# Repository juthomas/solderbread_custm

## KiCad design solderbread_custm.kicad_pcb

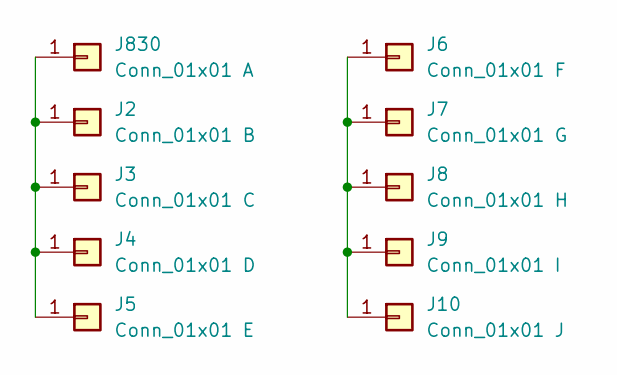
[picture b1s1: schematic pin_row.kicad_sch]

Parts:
J2: Conn_01x01 B; single_pin
J3: Conn_01x01 C; single_pin
J4: Conn_01x01 D; single_pin
J5: Conn_01x01 E; single_pin
J6: Conn_01x01 F; single_pin
J7: Conn_01x01 G; single_pin
J8: Conn_01x01 H; single_pin
J9: Conn_01x01 I; single_pin
J10: Conn_01x01 J; single_pin
J830: Conn_01x01 A; single_pin

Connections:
unnamed: J2.1, J3.1, J4.1, J5.1, J830.1
unnamed: J6.1, J7.1, J8.1, J9.1, J10.1

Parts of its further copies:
J11, J21, J31, J41, J51, J61, J71, J81, J91, J101, J111, J121, J131, J141, J151, J161, J171, J181, J191, J201, J211, J221, J231, J241, J251, J261, J271, J281, J291, J301, J311, J321, J331, J341, J351, J361, J371, J381, J391, J401, J411, J421, J431, J441, J451, J461, J471, J481, J491, J501, J511, J521, J531, J541, J551, J561, J571, J581, J591, J601, J611, J621: Conn_01x01 A; single_pin
J12, J22, J32, J42, J52, J62, J72, J82, J92, J102, J112, J122, J132, J142, J152, J162, J172, J182, J192, J202, J212, J222, J232, J242, J252, J262, J272, J282, J292, J302, J312, J322, J332, J342, J352, J362, J372, J382, J392, J402, J412, J422, J432, J442, J452, J462, J472, J482, J492, J502, J512, J522, J532, J542, J552, J562, J572, J582, J592, J602, J612, J622: Conn_01x01 B; single_pin
J13, J23, J33, J43, J53, J63, J73, J83, J93, J103, J113, J123, J133, J143, J153, J163, J173, J183, J193, J203, J213, J223, J233, J243, J253, J263, J273, J283, J293, J303, J313, J323, J333, J343, J353, J363, J373, J383, J393, J403, J413, J423, J433, J443, J453, J463, J473, J483, J493, J503, J513, J523, J533, J543, J553, J563, J573, J583, J593, J603, J613, J623: Conn_01x01 C; single_pin
J14, J24, J34, J44, J54, J64, J74, J84, J94, J104, J114, J124, J134, J144, J154, J164, J174, J184, J194, J204, J214, J224, J234, J244, J254, J264, J274, J284, J294, J304, J314, J324, J334, J344, J354, J364, J374, J384, J394, J404, J414, J424, J434, J444, J454, J464, J474, J484, J494, J504, J514, J524, J534, J544, J554, J564, J574, J584, J594, J604, J614, J624: Conn_01x01 D; single_pin
J15, J25, J35, J45, J55, J65, J75, J85, J95, J105, J115, J125, J135, J145, J155, J165, J175, J185, J195, J205, J215, J225, J235, J245, J255, J265, J275, J285, J295, J305, J315, J325, J335, J345, J355, J365, J375, J385, J395, J405, J415, J425, J435, J445, J455, J465, J475, J485, J495, J505, J515, J525, J535, J545, J555, J565, J575, J585, J595, J605, J615, J625: Conn_01x01 E; single_pin
J16, J26, J36, J46, J56, J66, J76, J86, J96, J106, J116, J126, J136, J146, J156, J166, J176, J186, J196, J206, J216, J226, J236, J246, J256, J266, J276, J286, J296, J306, J316, J326, J336, J346, J356, J366, J376, J386, J396, J406, J416, J426, J436, J446, J456, J466, J476, J486, J496, J506, J516, J526, J536, J546, J556, J566, J576, J586, J596, J606, J616, J626: Conn_01x01 F; single_pin
J17, J27, J37, J47, J57, J67, J77, J87, J97, J107, J117, J127, J137, J147, J157, J167, J177, J187, J197, J207, J217, J227, J237, J247, J257, J267, J277, J287, J297, J307, J317, J327, J337, J347, J357, J367, J377, J387, J397, J407, J417, J427, J437, J447, J457, J467, J477, J487, J497, J507, J517, J527, J537, J547, J557, J567, J577, J587, J597, J607, J617, J627: Conn_01x01 G; single_pin
J18, J28, J38, J48, J58, J68, J78, J88, J98, J108, J118, J128, J138, J148, J158, J168, J178, J188, J198, J208, J218, J228, J238, J248, J258, J268, J278, J288, J298, J308, J318, J328, J338, J348, J358, J368, J378, J388, J398, J408, J418, J428, J438, J448, J458, J468, J478, J488, J498, J508, J518, J528, J538, J548, J558, J568, J578, J588, J598, J608, J618, J628: Conn_01x01 H; single_pin
J19, J29, J39, J49, J59, J69, J79, J89, J99, J109, J119, J129, J139, J149, J159, J169, J179, J189, J199, J209, J219, J229, J239, J249, J259, J269, J279, J289, J299, J309, J319, J329, J339, J349, J359, J369, J379, J389, J399, J409, J419, J429, J439, J449, J459, J469, J479, J489, J499, J509, J519, J529, J539, J549, J559, J569, J579, J589, J599, J609, J619, J629: Conn_01x01 I; single_pin
J20, J30, J40, J50, J60, J70, J80, J90, J100, J110, J120, J130, J140, J150, J160, J170, J180, J190, J200, J210, J220, J230, J240, J250, J260, J270, J280, J290, J300, J310, J320, J330, J340, J350, J360, J370, J380, J390, J400, J410, J420, J430, J440, J450, J460, J470, J480, J490, J500, J510, J520, J530, J540, J550, J560, J570, J580, J590, J600, J610, J620, J630: Conn_01x01 J; single_pin

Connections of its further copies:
unnamed: J11.1, J12.1, J13.1, J14.1, J15.1
unnamed: J16.1, J17.1, J18.1, J19.1, J20.1
unnamed: J21.1, J22.1, J23.1, J24.1, J25.1
unnamed: J26.1, J27.1, J28.1, J29.1, J30.1
unnamed: J31.1, J32.1, J33.1, J34.1, J35.1
unnamed: J36.1, J37.1, J38.1, J39.1, J40.1
unnamed: J41.1, J42.1, J43.1, J44.1, J45.1
unnamed: J46.1, J47.1, J48.1, J49.1, J50.1
unnamed: J51.1, J52.1, J53.1, J54.1, J55.1
unnamed: J56.1, J57.1, J58.1, J59.1, J60.1
unnamed: J61.1, J62.1, J63.1, J64.1, J65.1
unnamed: J66.1, J67.1, J68.1, J69.1, J70.1
unnamed: J71.1, J72.1, J73.1, J74.1, J75.1
unnamed: J76.1, J77.1, J78.1, J79.1, J80.1
unnamed: J81.1, J82.1, J83.1, J84.1, J85.1
unnamed: J86.1, J87.1, J88.1, J89.1, J90.1
unnamed: J91.1, J92.1, J93.1, J94.1, J95.1
unnamed: J96.1, J97.1, J98.1, J99.1, J100.1
unnamed: J101.1, J102.1, J103.1, J104.1, J105.1
unnamed: J106.1, J107.1, J108.1, J109.1, J110.1
unnamed: J111.1, J112.1, J113.1, J114.1, J115.1
unnamed: J116.1, J117.1, J118.1, J119.1, J120.1
unnamed: J121.1, J122.1, J123.1, J124.1, J125.1
unnamed: J126.1, J127.1, J128.1, J129.1, J130.1
unnamed: J131.1, J132.1, J133.1, J134.1, J135.1
unnamed: J136.1, J137.1, J138.1, J139.1, J140.1
unnamed: J141.1, J142.1, J143.1, J144.1, J145.1
unnamed: J146.1, J147.1, J148.1, J149.1, J150.1
unnamed: J151.1, J152.1, J153.1, J154.1, J155.1
unnamed: J156.1, J157.1, J158.1, J159.1, J160.1
unnamed: J161.1, J162.1, J163.1, J164.1, J165.1
unnamed: J166.1, J167.1, J168.1, J169.1, J170.1
unnamed: J171.1, J172.1, J173.1, J174.1, J175.1
unnamed: J176.1, J177.1, J178.1, J179.1, J180.1
unnamed: J181.1, J182.1, J183.1, J184.1, J185.1
unnamed: J186.1, J187.1, J188.1, J189.1, J190.1
unnamed: J191.1, J192.1, J193.1, J194.1, J195.1
unnamed: J196.1, J197.1, J198.1, J199.1, J200.1
unnamed: J201.1, J202.1, J203.1, J204.1, J205.1
unnamed: J206.1, J207.1, J208.1, J209.1, J210.1
unnamed: J211.1, J212.1, J213.1, J214.1, J215.1
unnamed: J216.1, J217.1, J218.1, J219.1, J220.1
unnamed: J221.1, J222.1, J223.1, J224.1, J225.1
unnamed: J226.1, J227.1, J228.1, J229.1, J230.1
unnamed: J231.1, J232.1, J233.1, J234.1, J235.1
unnamed: J236.1, J237.1, J238.1, J239.1, J240.1
unnamed: J241.1, J242.1, J243.1, J244.1, J245.1
unnamed: J246.1, J247.1, J248.1, J249.1, J250.1
unnamed: J251.1, J252.1, J253.1, J254.1, J255.1
unnamed: J256.1, J257.1, J258.1, J259.1, J260.1
unnamed: J261.1, J262.1, J263.1, J264.1, J265.1
unnamed: J266.1, J267.1, J268.1, J269.1, J270.1
unnamed: J271.1, J272.1, J273.1, J274.1, J275.1
unnamed: J276.1, J277.1, J278.1, J279.1, J280.1
unnamed: J281.1, J282.1, J283.1, J284.1, J285.1
unnamed: J286.1, J287.1, J288.1, J289.1, J290.1
unnamed: J291.1, J292.1, J293.1, J294.1, J295.1
unnamed: J296.1, J297.1, J298.1, J299.1, J300.1
unnamed: J301.1, J302.1, J303.1, J304.1, J305.1
unnamed: J306.1, J307.1, J308.1, J309.1, J310.1
unnamed: J311.1, J312.1, J313.1, J314.1, J315.1
unnamed: J316.1, J317.1, J318.1, J319.1, J320.1
unnamed: J321.1, J322.1, J323.1, J324.1, J325.1
unnamed: J326.1, J327.1, J328.1, J329.1, J330.1
unnamed: J331.1, J332.1, J333.1, J334.1, J335.1
unnamed: J336.1, J337.1, J338.1, J339.1, J340.1
unnamed: J341.1, J342.1, J343.1, J344.1, J345.1
unnamed: J346.1, J347.1, J348.1, J349.1, J350.1
unnamed: J351.1, J352.1, J353.1, J354.1, J355.1
unnamed: J356.1, J357.1, J358.1, J359.1, J360.1
unnamed: J361.1, J362.1, J363.1, J364.1, J365.1
unnamed: J366.1, J367.1, J368.1, J369.1, J370.1
unnamed: J371.1, J372.1, J373.1, J374.1, J375.1
unnamed: J376.1, J377.1, J378.1, J379.1, J380.1
unnamed: J381.1, J382.1, J383.1, J384.1, J385.1
unnamed: J386.1, J387.1, J388.1, J389.1, J390.1
unnamed: J391.1, J392.1, J393.1, J394.1, J395.1
unnamed: J396.1, J397.1, J398.1, J399.1, J400.1
unnamed: J401.1, J402.1, J403.1, J404.1, J405.1
unnamed: J406.1, J407.1, J408.1, J409.1, J410.1
unnamed: J411.1, J412.1, J413.1, J414.1, J415.1
unnamed: J416.1, J417.1, J418.1, J419.1, J420.1
unnamed: J421.1, J422.1, J423.1, J424.1, J425.1
unnamed: J426.1, J427.1, J428.1, J429.1, J430.1
unnamed: J431.1, J432.1, J433.1, J434.1, J435.1
unnamed: J436.1, J437.1, J438.1, J439.1, J440.1
unnamed: J441.1, J442.1, J443.1, J444.1, J445.1
unnamed: J446.1, J447.1, J448.1, J449.1, J450.1
unnamed: J451.1, J452.1, J453.1, J454.1, J455.1
unnamed: J456.1, J457.1, J458.1, J459.1, J460.1
unnamed: J461.1, J462.1, J463.1, J464.1, J465.1
unnamed: J466.1, J467.1, J468.1, J469.1, J470.1
unnamed: J471.1, J472.1, J473.1, J474.1, J475.1
unnamed: J476.1, J477.1, J478.1, J479.1, J480.1
unnamed: J481.1, J482.1, J483.1, J484.1, J485.1
unnamed: J486.1, J487.1, J488.1, J489.1, J490.1
unnamed: J491.1, J492.1, J493.1, J494.1, J495.1
unnamed: J496.1, J497.1, J498.1, J499.1, J500.1
unnamed: J501.1, J502.1, J503.1, J504.1, J505.1
unnamed: J506.1, J507.1, J508.1, J509.1, J510.1
unnamed: J511.1, J512.1, J513.1, J514.1, J515.1
unnamed: J516.1, J517.1, J518.1, J519.1, J520.1
unnamed: J521.1, J522.1, J523.1, J524.1, J525.1
unnamed: J526.1, J527.1, J528.1, J529.1, J530.1
unnamed: J531.1, J532.1, J533.1, J534.1, J535.1
unnamed: J536.1, J537.1, J538.1, J539.1, J540.1
unnamed: J541.1, J542.1, J543.1, J544.1, J545.1
unnamed: J546.1, J547.1, J548.1, J549.1, J550.1
unnamed: J551.1, J552.1, J553.1, J554.1, J555.1
unnamed: J556.1, J557.1, J558.1, J559.1, J560.1
unnamed: J561.1, J562.1, J563.1, J564.1, J565.1
unnamed: J566.1, J567.1, J568.1, J569.1, J570.1
unnamed: J571.1, J572.1, J573.1, J574.1, J575.1
unnamed: J576.1, J577.1, J578.1, J579.1, J580.1
unnamed: J581.1, J582.1, J583.1, J584.1, J585.1
unnamed: J586.1, J587.1, J588.1, J589.1, J590.1
unnamed: J591.1, J592.1, J593.1, J594.1, J595.1
unnamed: J596.1, J597.1, J598.1, J599.1, J600.1
unnamed: J601.1, J602.1, J603.1, J604.1, J605.1
unnamed: J606.1, J607.1, J608.1, J609.1, J610.1
unnamed: J611.1, J612.1, J613.1, J614.1, J615.1
unnamed: J616.1, J617.1, J618.1, J619.1, J620.1
unnamed: J621.1, J622.1, J623.1, J624.1, J625.1
unnamed: J626.1, J627.1, J628.1, J629.1, J630.1

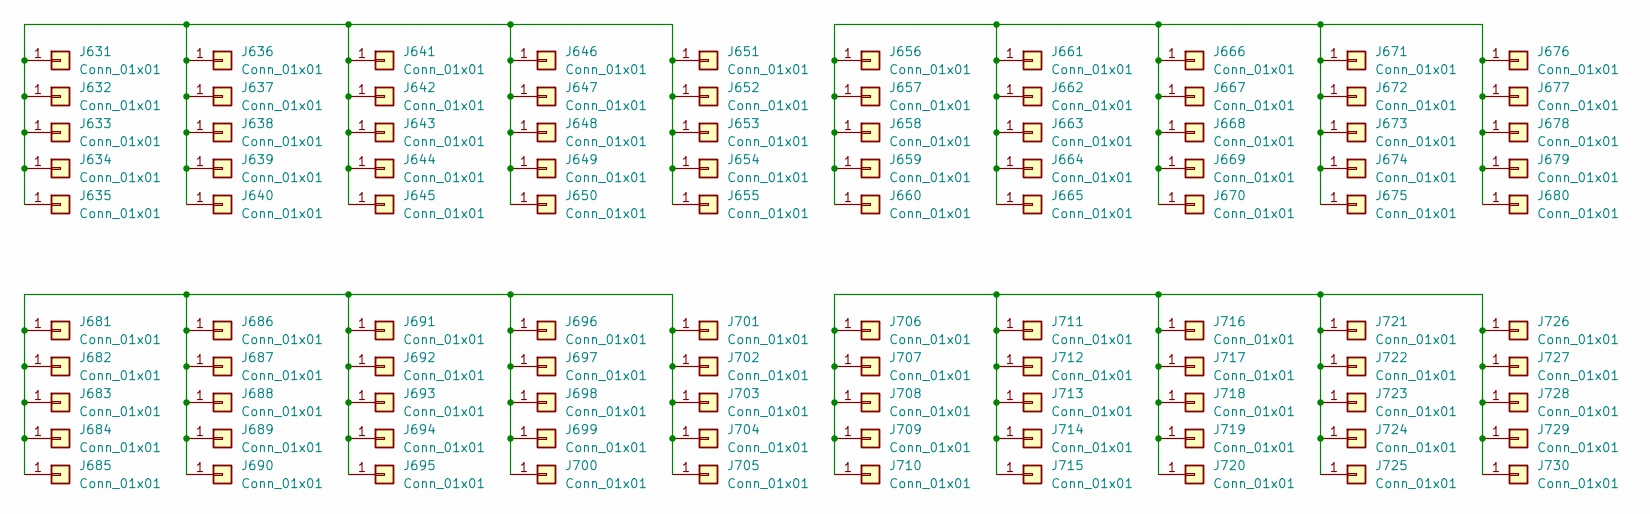
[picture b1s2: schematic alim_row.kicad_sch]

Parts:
J631, J632, J633, J634, J635, J636, J637, J638, J639, J640, J641, J642, J643, J644, J645, J646, J647, J648, J649, J650, J651, J652, J653, J654, J655, J656, J657, J658, J659, J660, J661, J662, J663, J664, J665, J666, J667, J668, J669, J670, J671, J672, J673, J674, J675, J676, J677, J678, J679, J680, J681, J682, J683, J684, J685, J686, J687, J688, J689, J690, J691, J692, J693, J694, J695, J696, J697, J698, J699, J700, J701, J702, J703, J704, J705, J706, J707, J708, J709, J710, J711, J712, J713, J714, J715, J716, J717, J718, J719, J720, J721, J722, J723, J724, J725, J726, J727, J728, J729, J730: Conn_01x01; single_pin

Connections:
unnamed: J631.1, J632.1, J633.1, J634.1, J635.1, J636.1, J637.1, J638.1, J639.1, J640.1, J641.1, J642.1, J643.1, J644.1, J645.1, J646.1, J647.1, J648.1, J649.1, J650.1, J651.1, J652.1, J653.1, J654.1, J655.1
unnamed: J656.1, J657.1, J658.1, J659.1, J660.1, J661.1, J662.1, J663.1, J664.1, J665.1, J666.1, J667.1, J668.1, J669.1, J670.1, J671.1, J672.1, J673.1, J674.1, J675.1, J676.1, J677.1, J678.1, J679.1, J680.1
unnamed: J681.1, J682.1, J683.1, J684.1, J685.1, J686.1, J687.1, J688.1, J689.1, J690.1, J691.1, J692.1, J693.1, J694.1, J695.1, J696.1, J697.1, J698.1, J699.1, J700.1, J701.1, J702.1, J703.1, J704.1, J705.1
unnamed: J706.1, J707.1, J708.1, J709.1, J710.1, J711.1, J712.1, J713.1, J714.1, J715.1, J716.1, J717.1, J718.1, J719.1, J720.1, J721.1, J722.1, J723.1, J724.1, J725.1, J726.1, J727.1, J728.1, J729.1, J730.1

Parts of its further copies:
J1, J731, J732, J733, J734, J735, J736, J737, J738, J739, J740, J741, J742, J743, J744, J745, J746, J747, J748, J749, J750, J751, J752, J753, J754, J755, J756, J757, J758, J759, J760, J761, J762, J763, J764, J765, J766, J767, J768, J769, J770, J771, J772, J773, J774, J775, J776, J777, J778, J779, J780, J781, J782, J783, J784, J785, J786, J787, J788, J789, J790, J791, J792, J793, J794, J795, J796, J797, J798, J799, J800, J801, J802, J803, J804, J805, J806, J807, J808, J809, J810, J811, J812, J813, J814, J815, J816, J817, J818, J819, J820, J821, J822, J823, J824, J825, J826, J827, J828, J829: Conn_01x01; single_pin

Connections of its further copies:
unnamed: J1.1, J731.1, J732.1, J733.1, J734.1, J740.1, J741.1, J742.1, J743.1, J744.1, J750.1, J751.1, J752.1, J753.1, J754.1, J760.1, J761.1, J762.1, J763.1, J764.1, J770.1, J771.1, J772.1, J773.1, J774.1
unnamed: J735.1, J736.1, J737.1, J738.1, J739.1, J745.1, J746.1, J747.1, J748.1, J749.1, J755.1, J756.1, J757.1, J758.1, J759.1, J765.1, J766.1, J767.1, J768.1, J769.1, J775.1, J776.1, J777.1, J778.1, J779.1
unnamed: J780.1, J781.1, J782.1, J783.1, J784.1, J790.1, J791.1, J792.1, J793.1, J794.1, J800.1, J801.1, J802.1, J803.1, J804.1, J810.1, J811.1, J812.1, J813.1, J814.1, J820.1, J821.1, J822.1, J823.1, J824.1
unnamed: J785.1, J786.1, J787.1, J788.1, J789.1, J795.1, J796.1, J797.1, J798.1, J799.1, J805.1, J806.1, J807.1, J808.1, J809.1, J815.1, J816.1, J817.1, J818.1, J819.1, J825.1, J826.1, J827.1, J828.1, J829.1

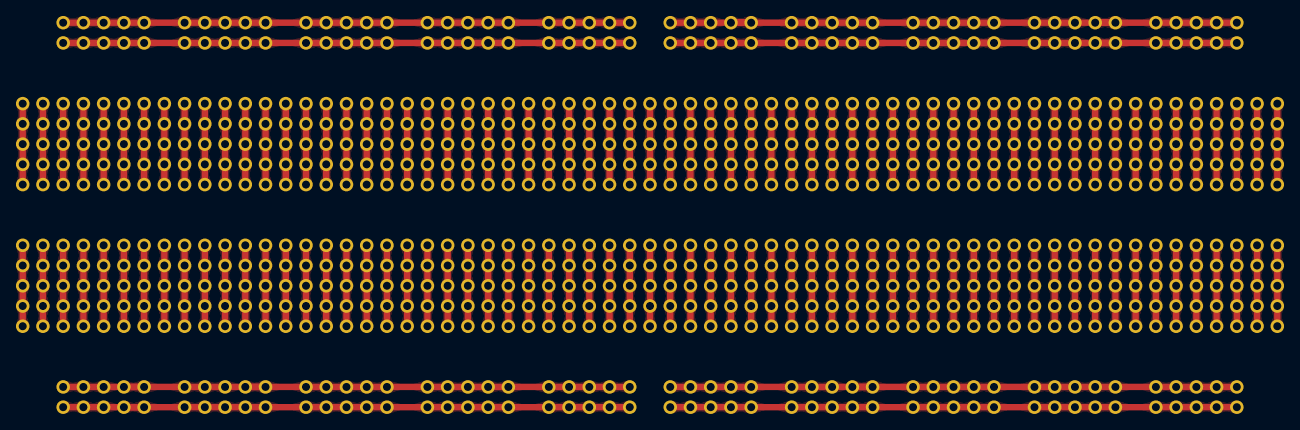
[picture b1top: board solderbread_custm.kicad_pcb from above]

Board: 2 copper layers, 830 parts (0 on the bottom side), 134 nets.

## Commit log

2025-05-16 [ADD] Basic Pin rows in pcb
2025-05-16 [ADD] footprints placed
2025-05-16 [ADD] Teardrops on top layer
